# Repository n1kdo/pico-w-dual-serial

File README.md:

# Pico-W Dual Serial 

This is a simple board that supports two RS-232 serial ports (TXD & RXD _only_) with a
Raspberry PI Pico-W.  This is useful to internet-enable devices that support a serial 
interface.

This board is sized for a [Hammond Manufacturing 1591XXSFLBK](https://www.hammfg.com/part/1591XXSFLBK) enclosure.

## Pictures

3-D image from Kicad 

Real board!

## Schematic and Bill of Materials

[Schematic PDF](schematic.pdf)

[Bill of Materials](Bill-of-Materials.md)

## License

This work is licensed under a
[Creative Commons Attribution-ShareAlike 4.0 International License](http://creativecommons.org/licenses/by-sa/4.0/).

To view a copy of this license, visit http://creativecommons.org/licenses/by-sa/4.0/ or send a letter to Creative Commons, PO Box 1866, Mountain View, CA 94042, USA.

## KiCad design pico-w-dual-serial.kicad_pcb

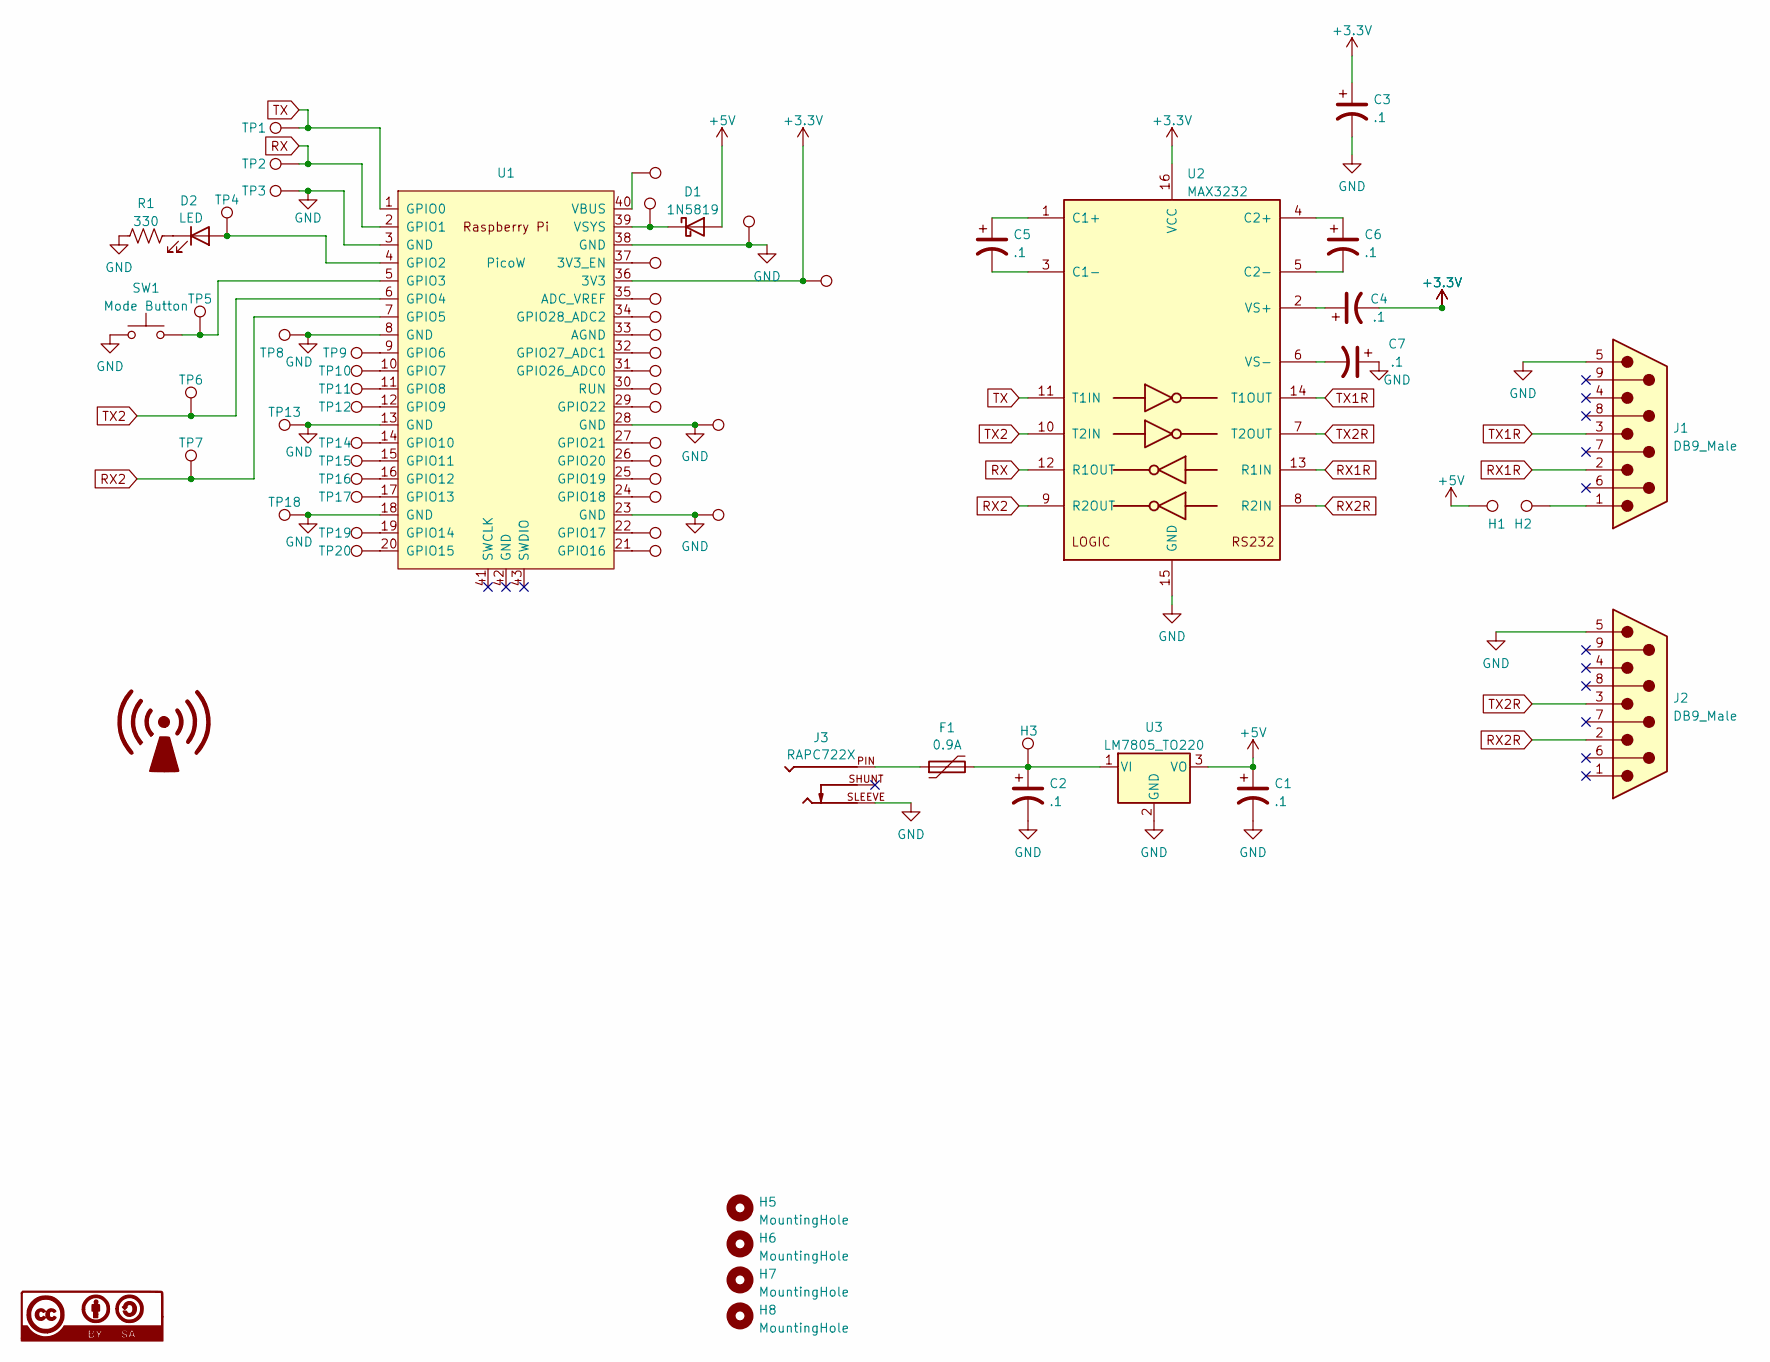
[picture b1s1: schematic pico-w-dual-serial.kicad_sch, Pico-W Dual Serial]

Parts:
C1, C2, C3, C4, C5, C6, C7: .1; CP_Radial_Tantal_D4.5mm_P2.50mm; part T350A104M035AT
D1: 1N5819; D_DO-41_SOD81_P7.62mm_Horizontal
D2: LED; LED_D3.0mm
F1: 0.9A; RUEF090
H1, H3: 2; TestPoint_THTPad_D1.5mm_Drill0.7mm
H2: 1; TestPoint_THTPad_D1.5mm_Drill0.7mm
H5, H6, H7, H8: MountingHole; MountingHole_3.5mm
J1, J2: DB9_Male; DSUB-9_Male_Horizontal_P2.77x2.84mm_EdgePinOffset4.94mm_Hou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; part L717SDE09PA4CH4RC309
J3: RAPC722X; SWITCHCRAFT_RAPC722X; PARTREV A
R1: 330; R_Axial_DIN0207_L6.3mm_D2.5mm_P7.62mm_Horizontal
SW1: Mode Button; GB215AHB; part GB215AH
TP1, TP2, TP3, TP4, TP5, TP6, TP7, TP8, TP9, TP10, TP11, TP12, TP13, TP14, TP15, TP16, TP17, TP18, TP19, TP20, TP21, TP22, TP23, TP24, TP25, TP26, TP27, TP28, TP29, TP30, TP31, TP32, TP33, TP34, TP35, TP36, TP37, TP38, TP39, TP40: TestPoint; TestPoint_THTPad_D1.5mm_Drill0.7mm
U1: PicoW; RPi_PicoW_SMD_TH
U2: MAX3232; DIP-16_W7.62mm_Socket
U3: LM7805_TO220; TO-220-3_Vertical

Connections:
+3.3V: C3.1, C4.2, TP36.1, U1.36 (3V3), U2.16 (VCC)
+5V: C1.1, D1.2 (A), H1.1, U3.3 (VO)
GND: C1.2, C2.2, C3.2, C7.1, J1.5, J2.5, J3.SLEEVE, R1.1, SW1.1, TP3.1, TP8.1, TP13.1, TP18.1, TP23.1, TP28.1, TP38.1, U1.3 (GND), U1.8 (GND), U1.13 (GND), U1.18 (GND), U1.23 (GND), U1.28 (GND), U1.38 (GND), U2.15 (GND), U3.2 (GND)
unnamed: D1.1 (K), TP39.1, U1.39 (VSYS)
unnamed: D2.2 (A), TP4.1, U1.4 (GPIO2)
unnamed: D2.1 (K), R1.2
unnamed: F1.1, J3.PIN
unnamed: H2.1, J1.1
unnamed: TP37.1, U1.37 (3V3_EN)
unnamed: TP35.1, U1.35 (ADC_VREF)
unnamed: TP33.1, U1.33 (AGND)
unnamed: SW1.2, TP5.1, U1.5 (GPIO3)
unnamed: TP9.1, U1.9 (GPIO6)
unnamed: TP10.1, U1.10 (GPIO7)
unnamed: TP11.1, U1.11 (GPIO8)
unnamed: TP12.1, U1.12 (GPIO9)
unnamed: TP14.1, U1.14 (GPIO10)
unnamed: TP15.1, U1.15 (GPIO11)
unnamed: TP16.1, U1.16 (GPIO12)
unnamed: TP17.1, U1.17 (GPIO13)
unnamed: TP19.1, U1.19 (GPIO14)
unnamed: TP20.1, U1.20 (GPIO15)
unnamed: TP21.1, U1.21 (GPIO16)
unnamed: TP22.1, U1.22 (GPIO17)
unnamed: TP24.1, U1.24 (GPIO18)
unnamed: TP25.1, U1.25 (GPIO19)
unnamed: TP26.1, U1.26 (GPIO20)
unnamed: TP27.1, U1.27 (GPIO21)
unnamed: TP29.1, U1.29 (GPIO22)
unnamed: TP31.1, U1.31 (GPIO26_ADC0)
unnamed: TP32.1, U1.32 (GPIO27_ADC1)
unnamed: TP34.1, U1.34 (GPIO28_ADC2)
unnamed: TP30.1, U1.30 (RUN)
unnamed: TP40.1, U1.40 (VBUS)
unnamed: C5.1, U2.1 (C1+)
unnamed: C5.2, U2.3 (C1-)
unnamed: C6.1, U2.4 (C2+)
unnamed: C6.2, U2.5 (C2-)
unnamed: C4.1, U2.2 (VS+)
unnamed: C7.2, U2.6 (VS-)
unnamed: C2.1, F1.2, H3.1, U3.1 (VI)
RX: TP2.1, U1.2 (GPIO1), U2.12 (R1OUT)
RX1R: J1.2, U2.13 (R1IN)
RX2: TP7.1, U1.7 (GPIO5), U2.9 (R2OUT)
RX2R: J2.2, U2.8 (R2IN)
TX: TP1.1, U1.1 (GPIO0), U2.11 (T1IN)
TX1R: J1.3, U2.14 (T1OUT)
TX2: TP6.1, U1.6 (GPIO4), U2.10 (T2IN)
TX2R: J2.3, U2.7 (T2OUT)

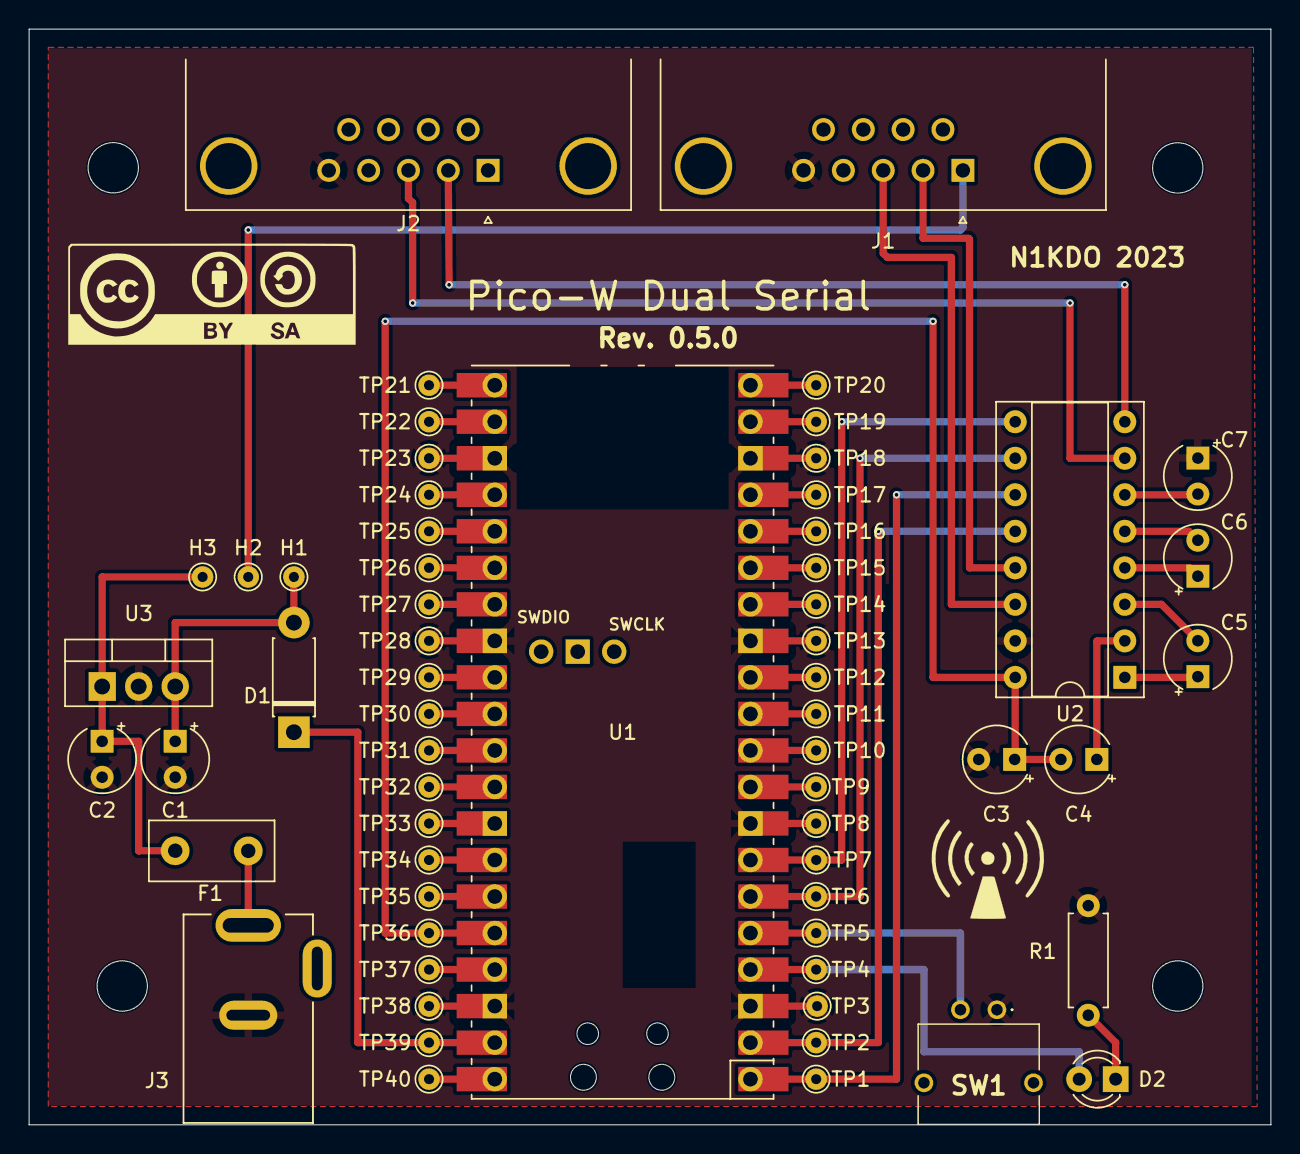
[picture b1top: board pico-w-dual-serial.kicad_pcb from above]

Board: 2 copper layers, 86.4 x 76.2 mm, 66 parts (0 on the bottom side), 49 nets.

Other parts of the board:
G1: LOGO; non-ionizing-bigger

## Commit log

2023-08-06 initial commit.
2023-08-06 add sexxy 3d image.
2023-08-06 add license file
2023-08-06 add enclosure information
2023-08-06 .gitignore
2023-08-06 fix typo
2023-08-14 fix reversed TX2/RX2
2023-08-29 new pic, better BOM
2023-09-02 validate design rules
2023-09-03 add bill of materials
2023-09-03 fix schematic, was missing text & etc.
2023-09-03 typo in license section of README.md
2023-09-03 link to BOM on README.md
2023-09-03 fix real image size.
2024-02-19 Create .gitattributes for github-linguist
    try to fix language detection.
    hide .kicad_sch files (there are one) on order taht
    .kicad_pcb files (there is also one) may be sufficient to trigger
    github-linguist to detect the repository is a kicad pcb

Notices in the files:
pico-w-dual-serial.kicad_pcb:
License CC-BY-SA https://creativecommons.org/licenses/by-sa/4.0
